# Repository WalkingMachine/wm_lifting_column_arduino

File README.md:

# Description
This repo contains a ROS driver to control a TimMotion TL5 linear actuator. There's a custom board between our driver and the lifting column. 

# Dependencies
* [Encoder.h](https://www.pjrc.com/teensy/td_libs_Encoder.html)

# Topics provided
* Subscriber
    * /column/cmd (std_msgs/Int32)
        * command can range from -255 (down) to 255 (up).
    * /column/set_position (std_msgs/Int32)
        * Allow to set the actual position
* Publisher
    * /column/position (std_msgs/Int32)
        * relative position from the hall sensor

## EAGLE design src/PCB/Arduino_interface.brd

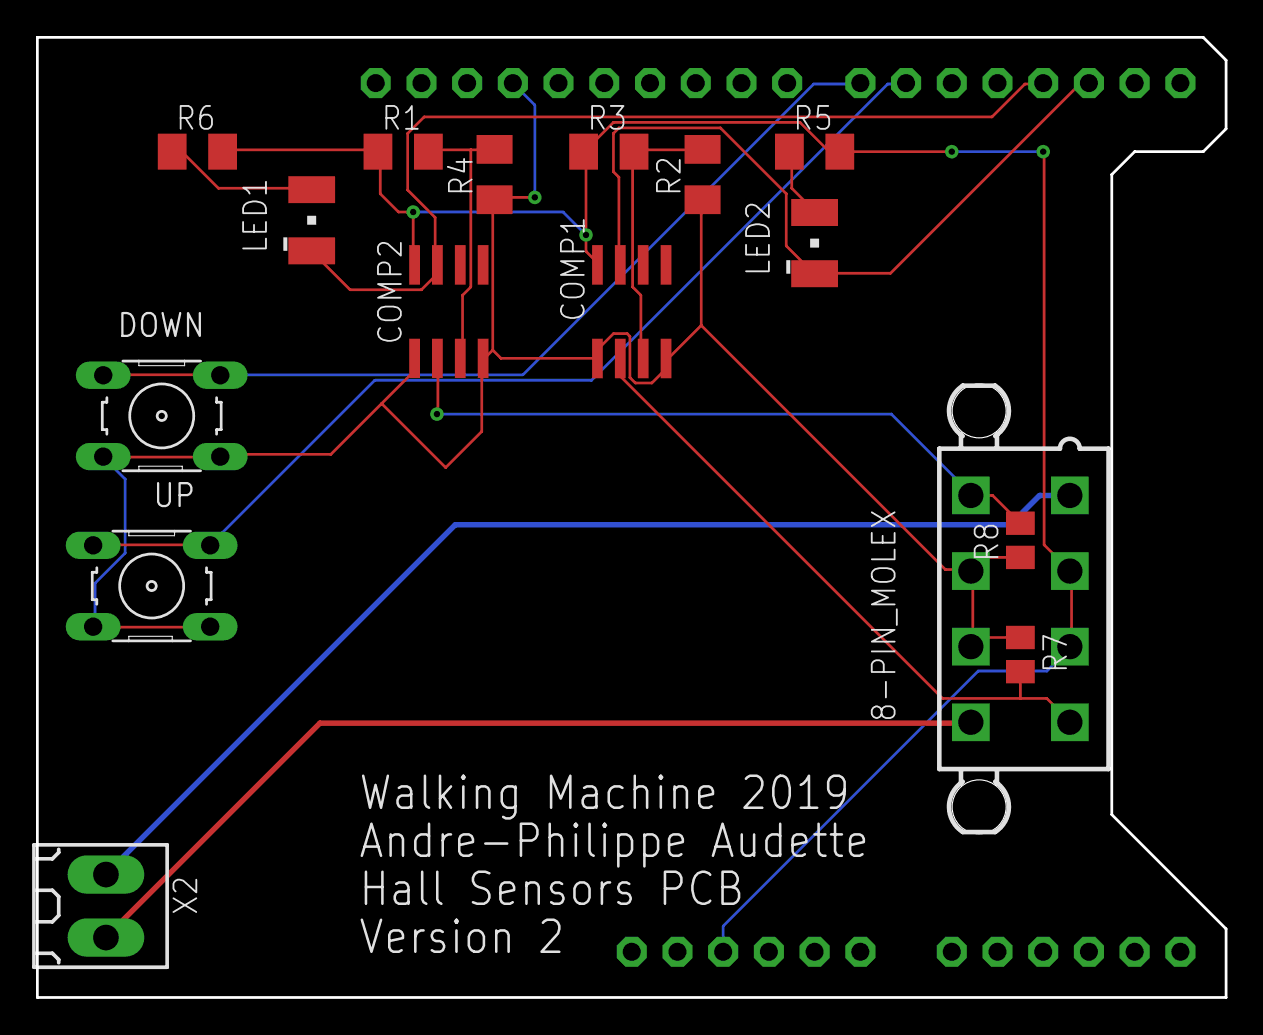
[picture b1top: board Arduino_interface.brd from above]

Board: 2 copper layers, 66.0 x 53.3 mm, 17 parts (0 on the bottom side), 14 nets.

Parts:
8-PIN_MOLEX: 5566-8
COMP1, COMP2: LM311D; SO08
DOWN: B3F-10XX
LED1, LED2: LG_T679-E1F1-1; PLCC2
Q1: ARDUINOR3-NOIOREF-NOTEXT; ARDUINOR3-NOTEXT-NOIOREF
R1, R3: 10 K; M1206
R2, R4, R5, R6: 1 K; M1206
R7, R8: 10 K; M0805
UP: B3F-10XX
X2: 180-2

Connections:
D6: Q1.D6, UP.1, UP.2
D7: DOWN.1, DOWN.2, Q1.D7
GND: 8-PIN_MOLEX.6, 8-PIN_MOLEX.7, COMP1.1, COMP1.4, COMP2.1, COMP2.4, DOWN.3, DOWN.4, Q1.GND, R2.1, R4.1, R7.1, R8.1, UP.3, UP.4
unnamed: COMP1.3, R2.2, R3.2
unnamed: COMP2.3, R1.2, R4.2
unnamed: 8-PIN_MOLEX.4, COMP1.2, R7.2
unnamed: 8-PIN_MOLEX.5, COMP2.2, R8.2
unnamed: 8-PIN_MOLEX.1, X2.1
unnamed: 8-PIN_MOLEX.8, X2.2
unnamed: LED2.A, R5.1
unnamed: LED1.A, R6.1
OUT1: COMP1.7, LED2.C, Q1.D2
OUT2: COMP2.7, LED1.C, Q1.D3
VCC: 8-PIN_MOLEX.2, 8-PIN_MOLEX.3, COMP1.8, COMP2.8, Q1.5V, R1.1, R3.1, R5.2, R6.2

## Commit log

2019-01-18 Ajoute le .ino initial
2019-01-18 fix un typo de ma part
2019-01-18 Arduino done, add ros pkg, start ros driver, add launch file
2019-01-20 Fix arduino code and state publisher UInt8->Int8
2019-01-20 Set true value for published position
2019-01-20 Add brackets
2019-01-20 change , to .
2019-01-20 Add set max topic
2019-01-23 Fix joint_state topic
2019-03-15 Velocity control + CLeanup
2019-03-16 Commit code
2019-04-08 Change frequency and init bug fix
2019-05-09 corrige une erreur d'addresse dans la EEPROM
2019-05-11 Détecte le non-mouvement de la colone pour sauvegarder dans la EEPROM au lieux de regarder la commande
2019-05-16 corrige un problème avec l'ecriture dans la EEPROM en utilisant une union
2019-05-20 réduit la vitesse de communication
2019-06-14 inverse les polaritées du hall sensor
2019-06-14 Utilise la commande pour déterminer la direction du mouvement Pour contourner le bug de pin disfonctionnelle
2019-06-18 met les bonnes valeurs pour UP et DOWN
2019-07-02 Ajout des fichiers du PCB de la colonne
2019-07-02 Rename src/Arduino_interface.brd to src/PCB/Arduino_interface.brd
2019-07-02 Rename src/Arduino_interface.sch to src/PCB/Arduino_interface.sch
2019-07-02 Rename src/PCB/Arduino_interface.brd to PCB/Arduino_interface.brd
2019-07-02 Rename src/PCB/Arduino_interface.sch to PCB/Arduino_interface.sch
2019-07-03 Auto Zero and Auto Max
2019-10-27 Create test
2019-10-27 Rename test to VL53L0X code
2019-10-27 ajuste les limites et la gestion des limites
2019-10-27 Ajoute une détection des limit switches pour le min et le max pour calibrer automatiquement
2019-11-02 Rewrite the arduino code
2019-11-02 remove useless src
2019-11-02 Corrige la sauvegarde de la position dans la EEPROM
